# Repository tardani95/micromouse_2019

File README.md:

View this project on [CADLAB.io](https://cadlab.io/project/1610). 

micromouse_2019

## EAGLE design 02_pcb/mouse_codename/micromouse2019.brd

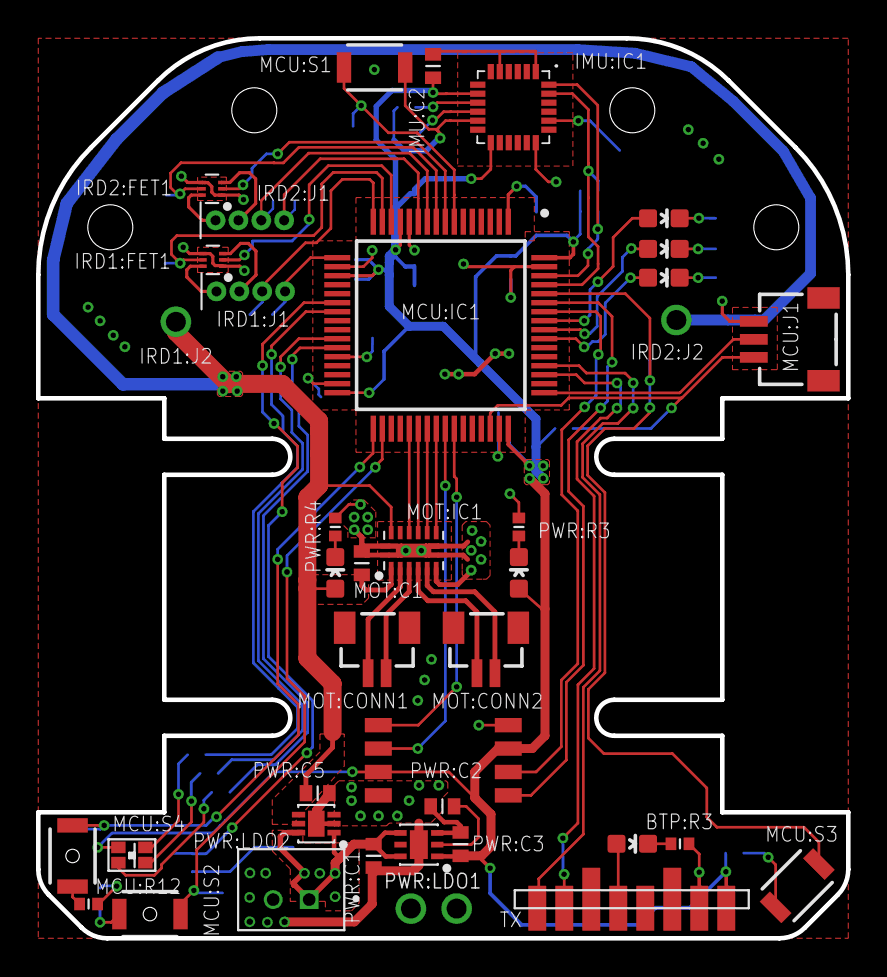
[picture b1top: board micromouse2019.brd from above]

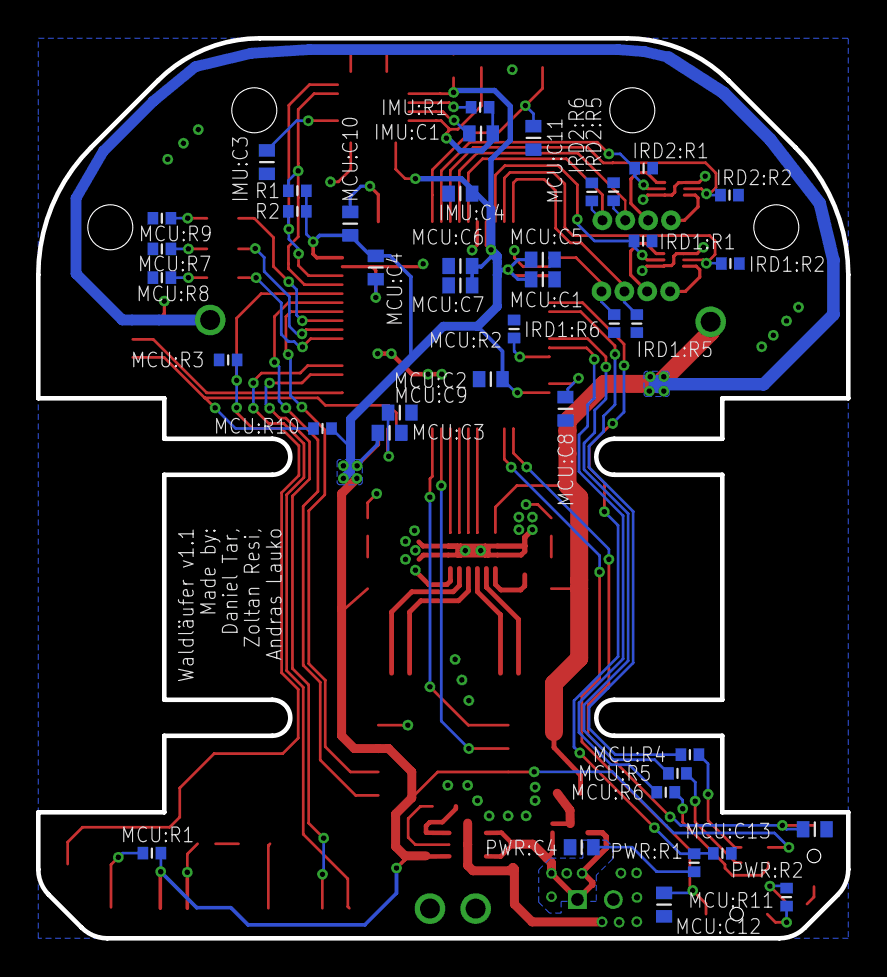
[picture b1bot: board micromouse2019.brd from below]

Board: 2 copper layers, 45.0 x 50.0 mm, 82 parts (41 on the bottom side), 66 nets.

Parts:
BTP:LED3: LED_B; 0603-BLUE
BTP:PORT1: PORT_BT_BASE; BT_PORT_BASE
BTP:R3: 100R; R0402
CONN1, CONN2: CONN_IRD_VCC; CONN_IRD_VCC_HDRV1W64P0_1X1_254X254X838B
EPL:PORT1: PORT_ENC_BASE; ENC_PORT_BASE
EPR:PORT1: PORT_ENC_BASE; ENC_PORT_BASE
IMU:C1, IMU:C2: 100n; C0402
IMU:C3: 2.2n; C0402
IMU:C4: 10n; C0402
IMU:IC1: IMU_MPU-6050; MPU6050
IMU:R1: 47k; R0402
IRD1:FET1, IRD2:FET1: FET_DMN2990UDJ-7; SOTFL35P100X50-6
IRD1:J1, IRD2:J1: CONN_IRDX4-P127; CONN_IRDX4_HDRV4W25P127_1X4_500X200X600B
IRD1:J2, IRD2:J2: CONN_IRD_VCC; CONN_IRD_VCC_HDRV1W64P0_1X1_254X254X838B
IRD1:R1, IRD1:R2, IRD2:R1, IRD2:R2: 10k; R0402
IRD1:R5, IRD1:R6, IRD2:R5, IRD2:R6: 2R; R0402
MCU:C1, MCU:C2, MCU:C3, MCU:C4, MCU:C6, MCU:C10, MCU:C11, MCU:C12, MCU:C13: 100n; C0402
MCU:C5: 4.7u; C0402
MCU:C7: 1u; C0402
MCU:C8, MCU:C9: 2.2u; C0402
MCU:IC1: MCU_STM32F405RGT6_L; QFP50P1200X1200X160-64N
MCU:J1: CONN_SWD; SM03B-SRSS-TB(LFSN)
MCU:LED1: LED_P; 0603-PINK
MCU:LED2: LED_G; 0603-GREEN
MCU:LED3: LED_Y; 0603-YELLOW
MCU:R1, MCU:R11, MCU:R12: 1k; R0402
MCU:R2, MCU:R3: 10k; R0402
MCU:R4, MCU:R9: 270R; R0402
MCU:R5, MCU:R6, MCU:R7, MCU:R8: 100R; R0402
MCU:R10: 100k; R0402
MCU:RGB1: LED_RGB-0603; D_RGB_0603
MCU:S1, MCU:S3: BTN_B3U-1000P; B3U-1000P
MCU:S2: BTN1; B3U-3000P
MCU:S4: BTN2; B3U-3000P
MOT:C1: 4u7; C0402
MOT:CONN1: MOTOR1; BM02B-SRSS-TB(LFSN)
MOT:CONN2: MOTOR2; BM02B-SRSS-TB(LFSN)
MOT:IC1: MOT_DRV88361; DRV8836
PWR:C1, PWR:C4: 1u; C0402
PWR:C2: 10n; C0402
PWR:C3: 2u2; C0402
PWR:C5: 10u; C0402
PWR:CONN1: CONN_BATTERY; JST_B2B-PH-K-S(LF)(SN)
PWR:LDO1: PS_TPS735DRVT; SON65P200X200X80-7T100X160
PWR:LDO2: PS_LDL112PU; SON50P200X200X80-7T92X145
PWR:LED1: LED_O; 0603-ORANGE
PWR:LED2: LED_R; 0603-RED
PWR:R1, PWR:R2: 47k; R0402
PWR:R3, PWR:R4: 270R; R0402
R1, R2: 4k7; R0402

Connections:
+3V3: BTP:PORT1.P$15, EPL:PORT1.P3, EPR:PORT1.P3, IMU:C2.1, IMU:C4.1, IMU:IC1.8, IMU:IC1.13, MCU:C1.1, MCU:C2.1, MCU:C3.1, MCU:C4.1, MCU:C5.1, MCU:C6.1, MCU:C7.1, MCU:C10.1, MCU:IC1.13, MCU:IC1.19, MCU:IC1.32, MCU:IC1.48, MCU:IC1.64, MCU:R1.2, MCU:R10.2, MCU:RGB1.P$1, PWR:C3.1, PWR:LDO1.1, PWR:LED1.A, R1.2, R2.2
BTP:BT_STATUS: BTP:LED3.A, BTP:PORT1.P$11
BTP:N$3: BTP:LED3.C, BTP:R3.2
DRV_A_IN1: MCU:IC1.37, MOT:IC1.10
DRV_A_IN2: MCU:IC1.38, MOT:IC1.9
DRV_B_IN1: MCU:IC1.39, MOT:IC1.8
DRV_B_IN2: MCU:IC1.40, MOT:IC1.7
ENC_LEFT_CHA: EPL:PORT1.P1, MCU:IC1.42
ENC_LEFT_CHB: EPL:PORT1.P2, MCU:IC1.41
ENC_RIGHT_CHA: EPR:PORT1.P1, MCU:IC1.59
ENC_RIGHT_CHB: EPR:PORT1.P2, MCU:IC1.58
GND: BTP:PORT1.P$14, BTP:R3.1, CONN1.1, CONN2.1, EPL:PORT1.P4, EPR:PORT1.P4, IMU:C1.2, IMU:C2.2, IMU:C3.2, IMU:C4.2, IMU:IC1.1, IMU:IC1.5, IMU:IC1.11, IMU:IC1.18, IMU:R1.1, IRD1:FET1.1, IRD1:FET1.4, IRD1:R1.1, IRD1:R2.1, IRD1:R5.1, IRD1:R6.1, IRD2:FET1.1, IRD2:FET1.4, IRD2:R1.1, IRD2:R2.1, IRD2:R5.1, IRD2:R6.1, MCU:C1.2, MCU:C2.2, MCU:C3.2, MCU:C4.2, MCU:C5.2, MCU:C6.2, MCU:C7.2, MCU:C8.2, MCU:C9.2, MCU:C11.2, MCU:C12.2, MCU:C13.2, MCU:IC1.12, MCU:IC1.18, MCU:IC1.63, MCU:J1.3, MCU:R2.1, MCU:R3.1, MCU:R7.2, MCU:R8.2, MCU:R9.2, MCU:R11.1, MCU:R12.1, MCU:S1.1, MOT:C1.2, MOT:IC1.6, MOT:IC1.14, MOT:IC1.15, MOT:IC1.16, MOT:IC1.17, PWR:C1.2, PWR:C2.2, PWR:C3.2, PWR:C4.2, PWR:C5.2, PWR:CONN1.2, PWR:LDO1.3, PWR:LDO1.7, PWR:LDO2.2, PWR:LDO2.7, PWR:R2.1, PWR:R3.1, PWR:R4.1
IMU:AD0: IMU:IC1.9, IMU:R1.2
IMU:CPOUT: IMU:C3.1, IMU:IC1.20
IMU:REGOUT: IMU:C1.1, IMU:IC1.10
IRD1:DRAIN_1: IRD1:FET1.6, IRD1:J1.1
IRD1:DRAIN_2: IRD1:FET1.3, IRD1:J1.2
IRD2:DRAIN_1: IRD2:FET1.6, IRD2:J1.1
IRD2:DRAIN_2: IRD2:FET1.3, IRD2:J1.2
MCU:BOOT0: MCU:IC1.60, MCU:R3.2, MCU:S3.1
MCU:BOOT1: MCU:IC1.28, MCU:R2.2
MCU:BTN1: MCU:C12.1, MCU:IC1.34, MCU:S2.1
MCU:BTN2: MCU:C13.1, MCU:IC1.33, MCU:S4.2
MCU:BTN_BOOT0: MCU:R1.1, MCU:S3.2
MCU:HEARTBEAT: MCU:IC1.55, MCU:LED2.A
MCU:LED_PINK: MCU:IC1.56, MCU:LED1.A
MCU:LED_YELLOW_SUBMARINE: MCU:IC1.57, MCU:LED3.A
MCU:N$1: MCU:R4.2, MCU:RGB1.P$2
MCU:N$2: MCU:LED1.C, MCU:R7.1
MCU:N$3: MCU:R5.2, MCU:RGB1.P$4
MCU:N$4: MCU:R6.2, MCU:RGB1.P$3
MCU:N$5: MCU:LED2.C, MCU:R8.1
MCU:N$6: MCU:LED3.C, MCU:R9.1
MCU:N$7: MCU:R11.2, MCU:S2.2
MCU:N$8: MCU:C8.1, MCU:IC1.31
MCU:N$9: MCU:R12.2, MCU:S4.1
MCU:N$10: MCU:C9.1, MCU:IC1.47
MCU:NRST: MCU:C11.1, MCU:IC1.7, MCU:S1.2
MCU:RGB_B: MCU:IC1.27, MCU:R6.1
MCU:RGB_G: MCU:IC1.26, MCU:R5.1
MCU:RGB_R: MCU:IC1.23, MCU:R4.1
MCU:SWCLK: MCU:IC1.49, MCU:J1.2
MCU:SWDIO: MCU:IC1.46, MCU:J1.1, MCU:R10.1
MCU:V_BAT: MCU:C10.2, MCU:IC1.1
MOT:AOUT1: MOT:CONN1.1, MOT:IC1.2
MOT:AOUT2: MOT:CONN1.2, MOT:IC1.3
MOT:BOUT1: MOT:CONN2.1, MOT:IC1.4
MOT:BOUT2: MOT:CONN2.2, MOT:IC1.5
unnamed: IRD1:FET1.2, IRD1:R1.2, MCU:IC1.14
unnamed: IRD1:FET1.5, IRD1:R2.2, MCU:IC1.15
unnamed: IRD1:J1.3, IRD1:R5.2, MCU:IC1.16
unnamed: IRD1:J1.4, IRD1:R6.2, MCU:IC1.17
unnamed: IRD2:FET1.2, IRD2:R1.2, MCU:IC1.8
unnamed: IRD2:FET1.5, IRD2:R2.2, MCU:IC1.9
unnamed: IRD2:J1.3, IRD2:R5.2, MCU:IC1.10
unnamed: IRD2:J1.4, IRD2:R6.2, MCU:IC1.11
PWR:N$1: PWR:C2.1, PWR:LDO1.2
PWR:N$2: PWR:LED1.C, PWR:R3.2
PWR:N$4: PWR:LED2.C, PWR:R4.2
PWR:V_BAT_IN: PWR:C1.1, PWR:C4.1, PWR:CONN1.1, PWR:LDO1.4, PWR:LDO1.6, PWR:LDO2.1, PWR:LDO2.6, PWR:R1.2
SCL: IMU:IC1.23, MCU:IC1.61, R1.1
SDA: IMU:IC1.24, MCU:IC1.62, R2.1
UART3_RX: BTP:PORT1.P$8, MCU:IC1.52
UART3_TX: BTP:PORT1.P$9, MCU:IC1.51
VCC: IRD1:J2.1, IRD2:J2.1, MOT:C1.1, MOT:IC1.1, MOT:IC1.12, PWR:C5.1, PWR:LDO2.4, PWR:LED2.A
V_BAT_LEVEL: MCU:IC1.22, PWR:R1.1, PWR:R2.2

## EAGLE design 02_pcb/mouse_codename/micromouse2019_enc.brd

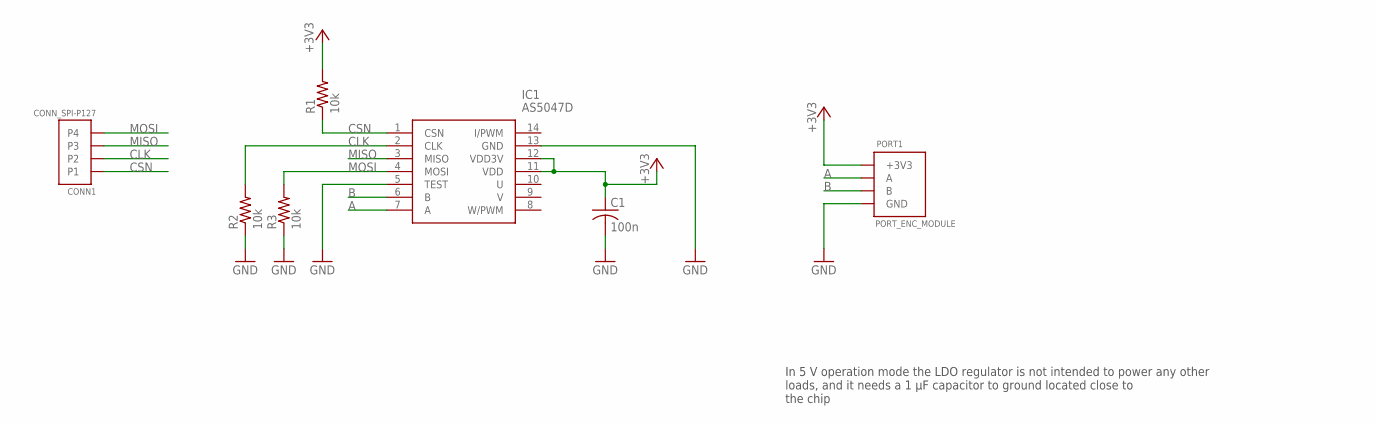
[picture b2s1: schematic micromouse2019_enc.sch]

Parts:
C1: 100n; C0402
CONN1: CONN_SPI-P127; CONN_SPI_HDRRA4W40P127_1X4_549X220X220B
IC1: AS5047D; SOP65P640X120-14N
PORT1: PORT_ENC_MODULE; ENC_PORT_MODULE
R1, R2, R3: 10k; R0402

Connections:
+3V3: C1.1, IC1.11 (VDD), IC1.12 (VDD3V), PORT1.P3 (+3V3), R1.2
A: IC1.7 (A), PORT1.P1 (A)
B: IC1.6 (B), PORT1.P2 (B)
CLK: CONN1.2, IC1.2 (CLK), R2.2
CSN: CONN1.1, IC1.1 (CSN), R1.1
GND: C1.2, IC1.5 (TEST), IC1.13 (GND), PORT1.P4 (GND), R2.1, R3.1
MISO: CONN1.3, IC1.3 (MISO)
MOSI: CONN1.4, IC1.4 (MOSI), R3.2

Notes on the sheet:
In 5 V operation mode the LDO regulator is not intended to power any other loads, and it needs a 1 μF capacitor to ground located close to the chip

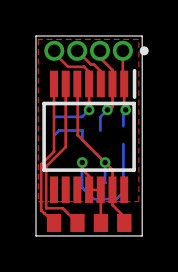
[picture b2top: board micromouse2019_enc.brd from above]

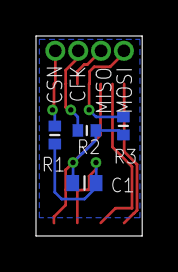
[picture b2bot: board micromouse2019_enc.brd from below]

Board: 2 copper layers, 5.9 x 11.1 mm, 7 parts (4 on the bottom side), 8 nets.

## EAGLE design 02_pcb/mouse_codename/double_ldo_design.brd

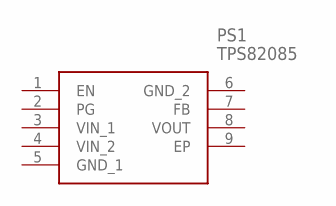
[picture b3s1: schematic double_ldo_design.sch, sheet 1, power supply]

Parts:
PS1: TPS82085

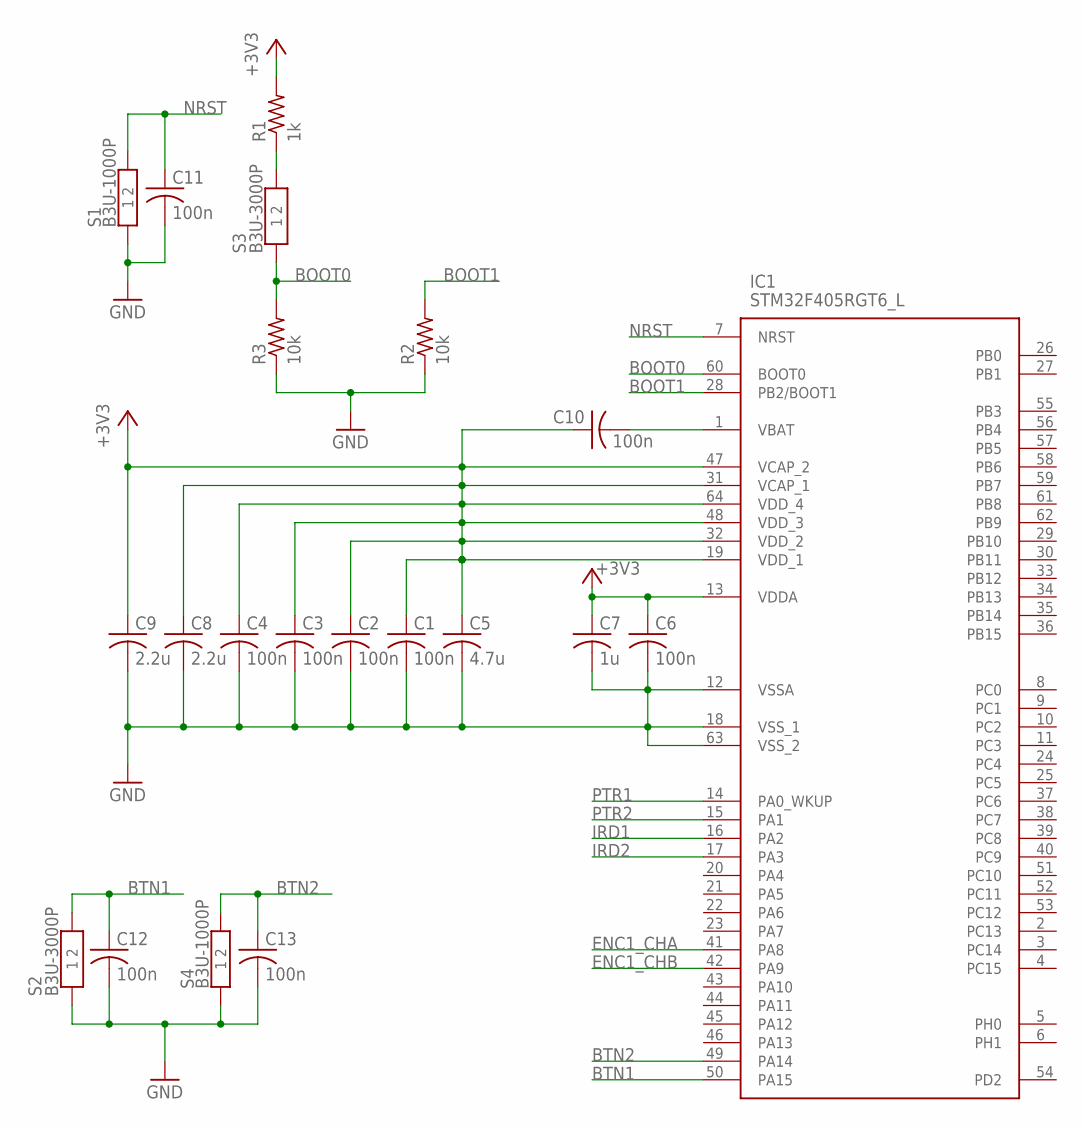
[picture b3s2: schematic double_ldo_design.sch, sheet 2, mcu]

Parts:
C1, C2, C3, C4, C6, C10, C11, C12, C13: 100n; C0402
C5: 4.7u; C0402
C7: 1u; C0402
C8, C9: 2.2u; C0402
IC1: STM32F405RGT6_L; QFP50P1200X1200X160-64N
R1: 1k; R0402
R2, R3: 10k; R0402
S1, S4: B3U-1000P
S2, S3: B3U-3000P

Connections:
+3V3: C1.1, C2.1, C3.1, C4.1, C5.1, C6.1, C7.1, C8.1, C9.1, C10.1, IC1.13 (VDDA), IC1.19 (VDD_1), IC1.31 (VCAP_1), IC1.32 (VDD_2), IC1.47 (VCAP_2), IC1.48 (VDD_3), IC1.64 (VDD_4), R1.2
BOOT0: IC1.60 (BOOT0), R3.2, S3.1
BOOT1: IC1.28 (PB2/BOOT1), R2.2
BTN1: C12.1, IC1.50 (PA15), S2.2
BTN2: C13.1, IC1.49 (PA14), S4.2
ENC1_CHA: IC1.41 (PA8)
ENC1_CHB: IC1.42 (PA9)
GND: C1.2, C2.2, C3.2, C4.2, C5.2, C6.2, C7.2, C8.2, C9.2, C11.2, C12.2, C13.2, IC1.12 (VSSA), IC1.18 (VSS_1), IC1.63 (VSS_2), R2.1, R3.1, S1.1, S2.1, S4.1
IRD1: IC1.16 (PA2)
IRD2: IC1.17 (PA3)
unnamed: R1.1, S3.2
unnamed: C10.2, IC1.1 (VBAT)
NRST: C11.1, IC1.7 (NRST), S1.2
PTR1: IC1.14 (PA0_WKUP)
PTR2: IC1.15 (PA1)

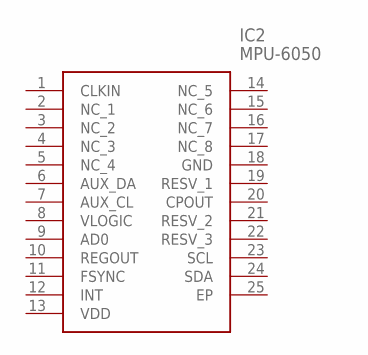
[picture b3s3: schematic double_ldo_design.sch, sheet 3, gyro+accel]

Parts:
IC2: MPU-6050; MPU6050

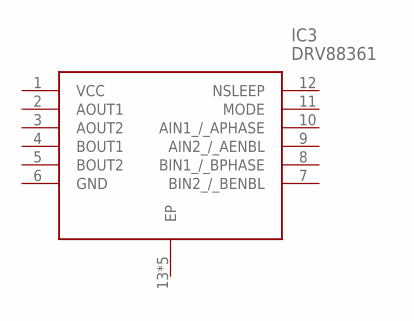
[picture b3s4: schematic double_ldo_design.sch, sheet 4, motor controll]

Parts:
IC3: DRV88361; DRV8836

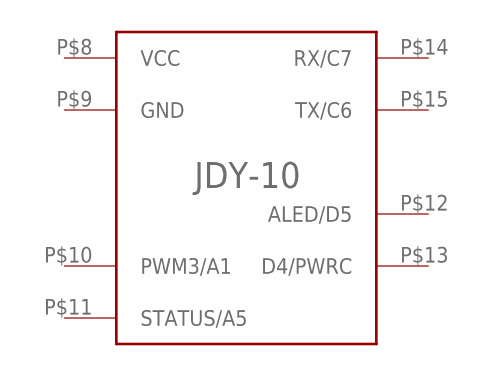
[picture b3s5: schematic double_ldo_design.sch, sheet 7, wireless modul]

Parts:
U$1: JDY-10_STANDING

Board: 2 copper layers, 25 parts (7 on the bottom side), 9 nets, no tracks yet.

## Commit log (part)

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2019-02-11 initial datasheets copied
2019-02-11 gitignore fixed
2019-02-11 gitignore updated
2019-02-12 datasheets updated
2019-02-12 previous schematic and bom excel added
2019-02-12 cubeMX project added
2019-02-12 eagle schematic and board layout added
2019-02-12 3D electric components added
2019-02-12 eagle board layout synced with fuison 360
2019-02-12 updated eagle files
2019-02-14 power consumption calculation
2019-02-14 3d files updated + added
2019-02-14 pcb board synced
2019-02-14 datasheets added, pcb libraries added
2019-02-19 3d modells added, updated
2019-02-19 eagle libraries updated, internal OC set with PLL
2019-02-19 pcb design updated
2019-02-19 cubeMX updated
2019-02-19 Backlink to CADLAB.io has been added.
2019-02-19 pcb updated
2019-02-20 mcu sheet updated
2019-02-20 frames added
2019-02-20 pins connected to buses
2019-02-20 battery voltage note added
2019-02-20 imu sheet updated
2019-02-20 serial wire debug added, buttons moved to another pin
2019-02-20 swd added
2019-02-20 f405 compatible processor, and additional notes on mcu
2019-02-20 dumy ir_ptr connector
2019-02-20 connectors moved
2019-02-20 .sch file repaired
2019-02-20 updated libraries
2019-02-20 LDO footprints updated
2019-02-20 PCB layout guidelines added
2019-02-20 Added step files for LDL and B2B
2019-02-20 added encoder schematic to project
2019-02-21 mosFET & IRLED_DRIVER added
    mosFET added to lib
    IRLED_DRIVER sheet added
2019-02-21 schematic and pcb created
2019-02-21 prepared for merge
2019-02-21 prepared for megre
2019-02-21 pcb updated with 3d components
2019-02-21 motor connector 3d file added
2019-02-21 3d modell files added
2019-02-21 main library updated with connectors
2019-02-21 motor sheet done + jlcpcb design rules
2019-02-21 parts moved
2019-02-21 cubeMx files organized
2019-02-21 fusion 360 synced
2019-02-22 Updated enc pcb, spi connector added
2019-02-22 enc PCB with correct measures
2019-02-22 Names and values on PCB arranged, values for R and C elements added
2019-02-22 increased size of enc port smds
2019-02-22 modules and buses
2019-02-22 encoder base moved to its place on pcb
2019-02-22 IR_PTR power supply voltage changed to VCC (bigger LDO)
2019-02-22 moduls connected
2019-02-22 bom file added - minior changes to pcb
2019-02-22 encoder pcb updated
2019-02-22 motor mode CHANGED to IN/IN, an PINs moved
2019-02-22 bat volt divider added, motor interface changed to IN/IN
2019-02-22 updated parts library (version 25) added
2019-02-22 enc_port_base orientation line added
2019-02-22 encoder moved to positon
2019-02-22 top level cosmetics
2019-02-22 new lib ebbe dolgoz zoli
2019-02-23 LDO comments
2019-02-23 rgb led added to cubeMX
2019-02-23 added BT_PORT to parts
2019-02-23 version controlled - not managed library
    import your parts from your managed library here
2019-02-23 schematic and board updated with the new common library
2019-02-23 Connectors added: IRD & IRDVCC & SPI
2019-02-23 encoder board libs replaced with 0-micromouse.lbr
2019-02-23 Connectors replaced: IRDx4 & IRDVCC & SPI
2019-02-23 rgb led added
2019-02-23 frame removed
2019-02-23 mcu condensator moved to position
2019-02-23 JDY changed to BT_PORT
2019-02-23 components moved to about position
2019-02-23 leds added
2019-02-23 second phase routing
2019-02-24 Enc pcb updated, design rules trace to dim updated
2019-02-24 updated all connectors
2019-02-24 IR LED module name shorter, resistor value corrections
2019-02-24 BT_PORT_BASE updated
2019-02-24 UART indicator LEDs removed
2019-02-24 IRD connectors repaired, IRD module split into 2
2019-02-24 IRD sheet notes added
2019-02-24 BTN_3000P drill added
2019-02-24 third phase routing
2019-02-24 BTN_3000p drill size corrected
2019-02-24 replaced pins
2019-02-24 LED & R & C footprint updated
2019-02-24 GPIO LEDs
2019-02-24 cubeMX pinout updated
2019-02-24 MOT_DRV footprint updated (therm)
2019-02-25 vcc routed
2019-02-25 MOT_DRV thermal pad via ready
2019-02-25 MOT_DRV thermal pad ready II.
    Conflicts resolved
2019-02-25 MOT_DRV thermal pad via ready II.
    Conflicts resolved
2019-02-25 lib updated
2019-02-25 pcb routing alpha v1_0
2019-02-25 button fix, drv8836 exposed pad fix
2019-02-25 bt_port tx rx changed
2019-02-25 Schematic approved by Zoli. IMU2 Removed. RGB attributes added
2019-02-25 module names shorter
2019-02-25 fets moved downwards
2019-02-25 LED 3D models added
2019-02-25 FET & LDO 3D models added
2019-02-25 leds updated
2019-02-25 3d packages update
2019-02-25 Libs updated
2019-02-25 MOT_DRV mode pin changed to IN/IN
2019-02-25 CONN_SPI 3d model added
2019-02-25 ratnest pcb pushed to fusion
2019-02-25 ENC A B channels repaired
2019-02-25 mot drv wire stub removed
2019-02-26 100k resistor added to SWDIO for bidirectional managment
2019-02-26 Footprint text size set 32 mil
2019-02-26 tNames sized and placed to position
2019-02-26 drc rule check ok
2019-02-26 3D modells updated
2019-02-26 project gant diagramm added
2019-02-26 Button footprint points removed
2019-02-26 datasheets updated 2
2019-02-26 FET thermal ground added & LDOs & FET variant names corrected
2019-02-26 mpu 6050 library fixed
2019-02-26 mpu6050 board layout fix
2019-02-26 board updated, strange polygon clearances
2019-02-26 top ground plane isolate set
2019-02-26 extra polygon deleted
2019-02-26 I2C pull up R on bottom & GND connection
2019-02-26 DRV Nsleep Vcc connect
2019-02-26 IMU EP removed & MCU_C11 & GND plane position adjustments
2019-02-27 Bogyo removed
2019-02-27 DRVCapacitor replaced & vias repositioned
2019-02-27 enc spi texts
2019-02-27 enc spi texts v2
2019-02-27 minior fixes
2019-02-27 some updates
2019-02-27 minor board updates
2019-02-27 text repositioning
2019-02-27 lipo battery comarision added
2019-03-04 initial CPP software with SPL (standard peripheral library)
2019-03-04 initial C software with SPL (standard peripheral library)
2019-03-05 initial C software with HAL (hardware abstraction layer)
2019-03-06 system core clock set to pll and 168 Mhz frequency set
2019-03-06 dma set in cubeMX
2019-03-06 language setttings xml for atollic studio setup
2019-03-06 project file set to compile and link library files
2019-03-06 removed unused peripheral headers + main formatted using autoformatter
    shift+ctrl+f - autoformat
2019-03-06 documentation subfiles added to gitignore
2019-03-06 updated pdf and .gitignore
    only update pdf if necessary
2019-03-08 peripheral initialization outline aded
2019-03-08 mainPage added to doxygen + @addgroup , @defgroup commands
2019-03-08 updated doxyfile
2019-03-08 hardware modules added
2019-03-08 library header files added
2019-03-08 library source filed added
2019-03-08 project outline created
2019-03-09 Menu macros added, main menu defined
2019-03-10 Added doxy documentation to menu
2019-03-11 Added after run menu
2019-03-11 #10 - button handling done
2019-03-12 encoder init code added
2019-03-13 status leds initialization added
2019-03-13 st_led code fixes, motor_ctrl init and basic ctrl fnc added
2019-03-14 added IR init and handling functions
2019-03-14 mpu6050 i2c test done
2019-03-14 bat lvlv watcher and debug writer added
2019-03-14 minor change in dbg
2019-03-15 bt communication and dbg macros checked
2019-03-15 button init fixed
2019-03-15 gitignore update
2019-03-15 LED pwm fixed (wasnt easy)
2019-03-15 motor control working
2019-03-15 bat_voltage_watcher working
2019-03-15 encoder interface working
2019-03-15 .cproject ignored
2019-03-15 .cproject tracking stopped
2019-03-18 menu working
2019-03-18 added ack system to ble communication dbg_cat changed to verbosity
2019-03-19 uart communication pc targets added
2019-03-28 imu test initial commit
2019-03-28 .cproject file restored
2019-03-28 clock source set to external 8mhz crystal
2019-03-29 system core clock fixed - i2c working perfectly
2019-03-29 all peripheral enabled - button2 messing with button1
2019-03-29 v_cap condesators connection fixed + name and made by texts added
2019-04-04 Auto stash before merge of "master" and "origin/master"
2019-04-08 .cproject tooolchainpathstring changed to local
2019-04-09 missing sources resolved
2019-04-09 mouse program updated to work with bootloader
2019-04-09 bootcommander added to git
2019-04-10 works with polling dma flags
2019-04-10 works without clearing the uart tc flag
2019-04-10 works with dma interrupt
2019-04-10 fully works with dma it
2019-04-11 uart dma checked
2019-04-12 uart rx and tx with dma
    receive first data length then data
2019-04-12 uart dma handling moved to it's lib files
2019-04-12 trying to write but not succesfull
2019-04-13 bootloader configured for stm32f407vg
2019-04-13 new imu lib and fixed an error in old one
2019-04-13 imu dma communication works
2019-04-13 minior fix with bluetooth module lib
2019-04-13 imu datasheets added
2019-04-13 uart dma init cleaned up a bit
2019-04-13 i2c dma fifo enabled
2019-04-13 main cleaned up and half word fifo added to i2c - need to fix
2019-04-13 halfword fifo is not possible because DMA controller only copes with little-endian addressing
2019-04-13 util lib extended with delay and timeout functionalities
2019-04-13 comments added to bluetooth lib
2019-04-19 1k resistor needed to put between the buttons and the ground
2019-04-19 button fix on pcb
2019-04-19 resistors repositioned
2019-04-24 IR module extended with calib functions
2019-04-24 communication module added
2019-04-24 for measurement unnecessary init functions commented
2019-04-24 send receive functions renamed
2019-04-24 IR module calib function measure calib function updated
2019-05-15 motors tested - actuateMotors function fault - with pure timers working
2019-05-15 encoder interface init function fixed
2019-05-15 encoders counting direction fixed
2019-05-16 adc testing for each channel
2019-05-17 IR led order fix
2019-05-17 adc bug - with single mod working, discontinuous mode not
2019-05-19 core clock header corrected - we are operating with 160MHz
2019-05-19 sysclock constants corrected
2019-05-19 adc discontinous mode fixed
2019-05-19 1kHz control loop skeleton added
2019-05-20 new motor control functions
2019-05-20 dummy control loop for encoders, button exti toggle fix
2019-05-20 cubemx clock constants syncronizied
2019-05-20 IR LED needs a 10-25us rise time
2019-05-21 adc common lib added
2019-05-21 ADCs working simultan
2019-05-21 IR module and batLvlWatcher encapsulated in ADC module
2019-05-21 status LED modifier functions structure changed
2019-05-21 low level and shutdown voltage irq handler created
2019-05-21 adc end of conversion interrupt set and delay with timer prepared
2019-05-21 updated voltage levels
2019-05-22 adc timer corrected according to measurements
2019-05-22 status led modifier functions speed up with direct register access
2019-05-22 doxygen adc modul update
2019-05-22 measurements with IMU
2019-05-22 changes, dunno what
2019-05-22 us polling timer added to util
2019-05-22 control with steadystate gains
2019-05-22 cubemx timers added
2019-05-23 new uart sending functions
2019-05-23 function names updated and global variables declared for debugging
2019-05-23 code format and todos done or removed
2019-05-23 old functions marked deprecated
2019-05-28 java maze visualizer submodule added
2019-05-28 port mediator submodule added
2019-06-03 new data model in maze visualizer submodule
2019-06-19 debug fnc added, sendDebug started
2019-06-19 debug data announce and send functions created
2019-06-20 debug fnc errors resolved
2019-06-20 sending on uart thru cyclical data buffer
2019-06-24 tobytes conversion now works
2019-06-24 build errors solved
2019-06-24 debug folder removed from git
2019-06-24 soha jobb még nem volt a bootloader
2019-06-25 bootloader works with ble ack
2019-07-06 BT communication bug fixes
2019-08-04 debug data publishing works
2019-08-04 added localization module
2019-08-04 params measurement units changed to cm
2019-08-04 encoder odometry added
2019-08-04 trajecorty planner module added
2019-08-04 maze and route planner modules added
2019-08-04 straight v_tan control added
2019-08-04 normal control added to straight trajectory
2019-08-04 rebase onto localization
2019-08-04 maze module cell struct and functions
2019-08-04 maze module cell struct and functions fix1
2019-08-04 new control finished
2019-08-11 stamp util
2019-08-11 localization global vars fix
